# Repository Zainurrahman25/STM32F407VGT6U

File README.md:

# STM32F407VGT6U
Project STM32F4

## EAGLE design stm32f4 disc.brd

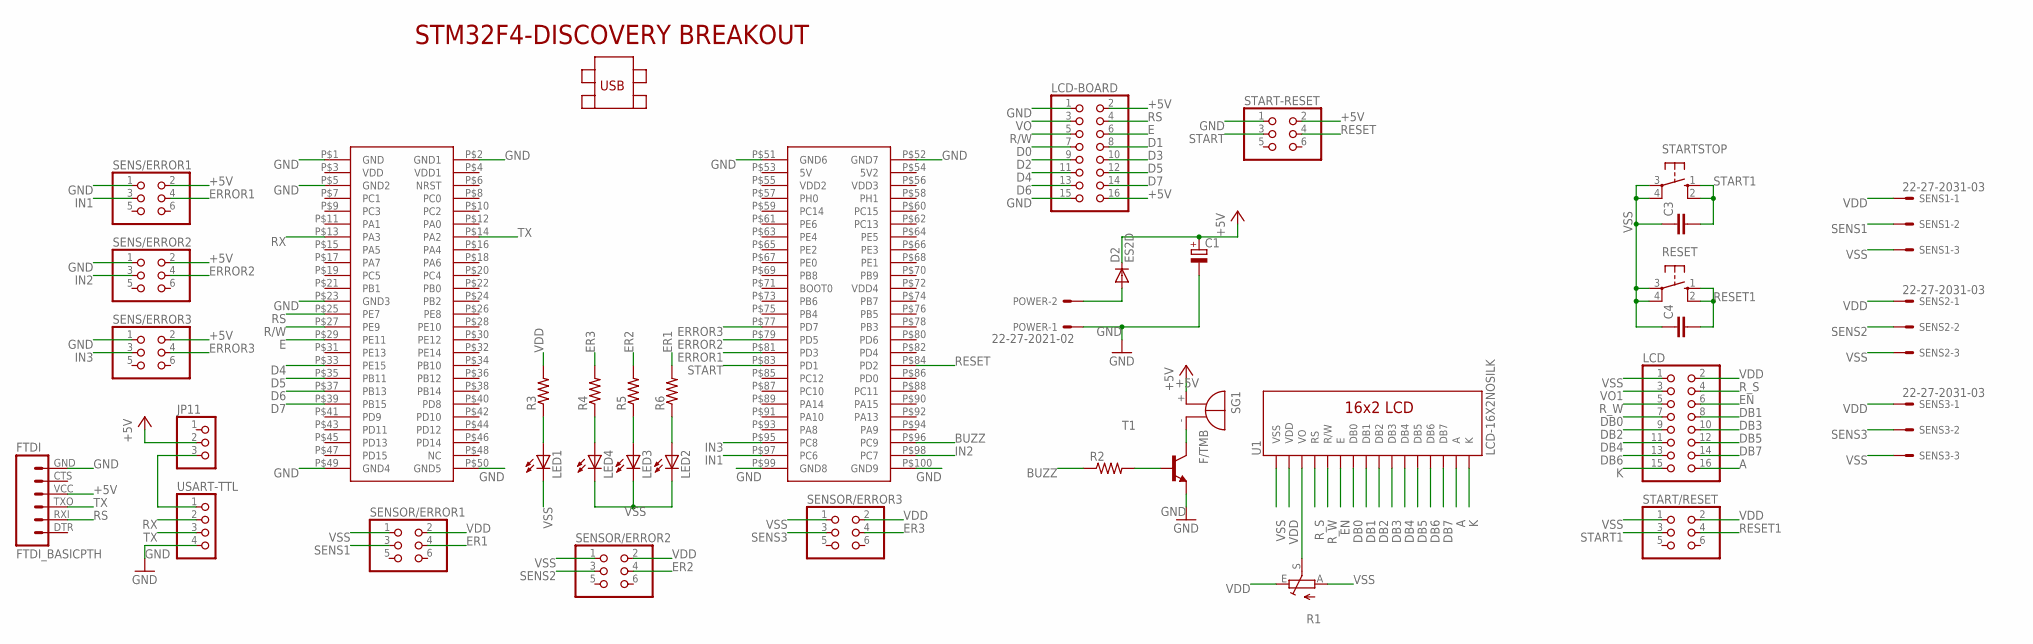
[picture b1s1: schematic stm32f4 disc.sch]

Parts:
C1: CPOL-EU140CLH-1010; 140CLH-1010
C3, C4: C-EUC0805; C0805
D2: ES2D; SMB
FTDI: FTDI_BASICPTH; FTDI_BASIC
JP11: PINHD-1X3; 1X03
LCD: PINHD-2X8; 2X08
LCD-BOARD: PINHD-2X8; 2X08
LED1, LED2, LED3, LED4: LED5MM
POWER: 22-27-2021-02; 6410-02
R1: TRIM_EU-CA6V; CA6V
R2, R3, R4, R5, R6: R-US_R0805; R0805
RESET: 40-XX; B3F-40XX
SENS1, SENS2, SENS3: 22-27-2031-03; 6410-03
SENS/ERROR1, SENS/ERROR2, SENS/ERROR3: PINHD-2X3; 2X03
SENSOR/ERROR1, SENSOR/ERROR2, SENSOR/ERROR3: PINHD-2X3; 2X03
SG1: F/TMB
START-RESET: PINHD-2X3; 2X03
START/RESET: PINHD-2X3; 2X03
STARTSTOP: 40-XX; B3F-40XX
T1: -NPN-SOT23-EBC; SOT23-EBC
U1: LCD-16X2NOSILK; LCD-16X2_NOSILK
U$1: STM32F4-DISCOVERY
USART-TTL: PINHD-1X4; 1X04

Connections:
+5V: C1.+, D2.C, FTDI.VCC (4), JP11.2, LCD-BOARD.2, LCD-BOARD.16, SENS/ERROR1.2, SENS/ERROR2.2, SENS/ERROR3.2, SG1.+, START-RESET.2
A: LCD.16, U1.15 (A)
BUZZ: R2.1, U$1.P$96 (PC9)
D0: LCD-BOARD.7
D1: LCD-BOARD.8
D2: LCD-BOARD.9
D3: LCD-BOARD.10
D4: LCD-BOARD.11, U$1.P$33 (PE15)
D5: LCD-BOARD.12, U$1.P$35 (PB11)
D6: LCD-BOARD.13, U$1.P$37 (PB13)
D7: LCD-BOARD.14, U$1.P$39 (PB15)
DB0: LCD.7, U1.7 (DB0)
DB1: LCD.8, U1.8 (DB1)
DB2: LCD.9, U1.9 (DB2)
DB3: LCD.10, U1.10 (DB3)
DB4: LCD.11, U1.11 (DB4)
DB5: LCD.12, U1.12 (DB5)
DB6: LCD.13, U1.13 (DB6)
DB7: LCD.14, U1.14 (DB7)
E: LCD-BOARD.6, U$1.P$29 (PE11)
EN: LCD.6, U1.6 (E)
ER1: R6.2, SENSOR/ERROR1.4
ER2: R5.2, SENSOR/ERROR2.4
ER3: R4.2, SENSOR/ERROR3.4
ERROR1: SENS/ERROR1.4, U$1.P$81 (PD3)
ERROR2: SENS/ERROR2.4, U$1.P$79 (PD5)
ERROR3: SENS/ERROR3.4, U$1.P$77 (PD7)
GND: C1.-, FTDI.GND (6), LCD-BOARD.1, LCD-BOARD.15, POWER.1, SENS/ERROR1.1, SENS/ERROR2.1, SENS/ERROR3.1, START-RESET.1, T1.E, U$1.P$1 (GND), U$1.P$2 (GND1), U$1.P$5 (GND2), U$1.P$23 (GND3), U$1.P$49 (GND4), U$1.P$50 (GND5), U$1.P$51 (GND6), U$1.P$52 (GND7), U$1.P$99 (GND8), U$1.P$100 (GND9), USART-TTL.4
IN1: SENS/ERROR1.3, U$1.P$97 (PC6)
IN2: SENS/ERROR2.3, U$1.P$98 (PC7)
IN3: SENS/ERROR3.3, U$1.P$95 (PC8)
K: LCD.15, U1.16 (K)
unnamed: SG1.-, T1.C
unnamed: R2.2, T1.B
unnamed: LED2.A, R6.1
unnamed: LED3.A, R5.1
unnamed: JP11.3, USART-TTL.1
unnamed: LED4.A, R4.1
unnamed: LED1.A, R3.1
unnamed: D2.A, POWER.2
unnamed: R1.S, U1.3 (VO)
R/W: LCD-BOARD.5, U$1.P$27 (PE9)
RESET: START-RESET.4, U$1.P$84 (PD2)
RESET1: C4.2, RESET.1 (S), RESET.2 (S1), START/RESET.4
RS: FTDI.RXI (2), LCD-BOARD.4, U$1.P$25 (PE7)
RX: U$1.P$13 (PA3), USART-TTL.2
R_S: LCD.4, U1.4 (RS)
R_W: LCD.5, U1.5 (R/W)
SENS1: SENS1.2, SENSOR/ERROR1.3
SENS2: SENS2.2, SENSOR/ERROR2.3
SENS3: SENS3.2, SENSOR/ERROR3.3
START: START-RESET.3, U$1.P$83 (PD1)
START1: C3.2, START/RESET.3, STARTSTOP.1 (S), STARTSTOP.2 (S1)
TX: FTDI.TXO (3), U$1.P$14 (PA2), USART-TTL.3
VDD: LCD.2, R1.E, R3.2, SENS1.1, SENS2.1, SENS3.1, SENSOR/ERROR1.2, SENSOR/ERROR2.2, SENSOR/ERROR3.2, START/RESET.2, U1.2 (VDD)
VO: LCD-BOARD.3
VO1: LCD.3
VSS: C3.1, C4.1, LCD.1, LED1.K (C), LED2.K (C), LED3.K (C), LED4.K (C), R1.A, RESET.3, RESET.4 (P1), SENS1.3, SENS2.3, SENS3.3, SENSOR/ERROR1.1, SENSOR/ERROR2.1, SENSOR/ERROR3.1, START/RESET.1, STARTSTOP.3, STARTSTOP.4 (P1), U1.1 (VSS)

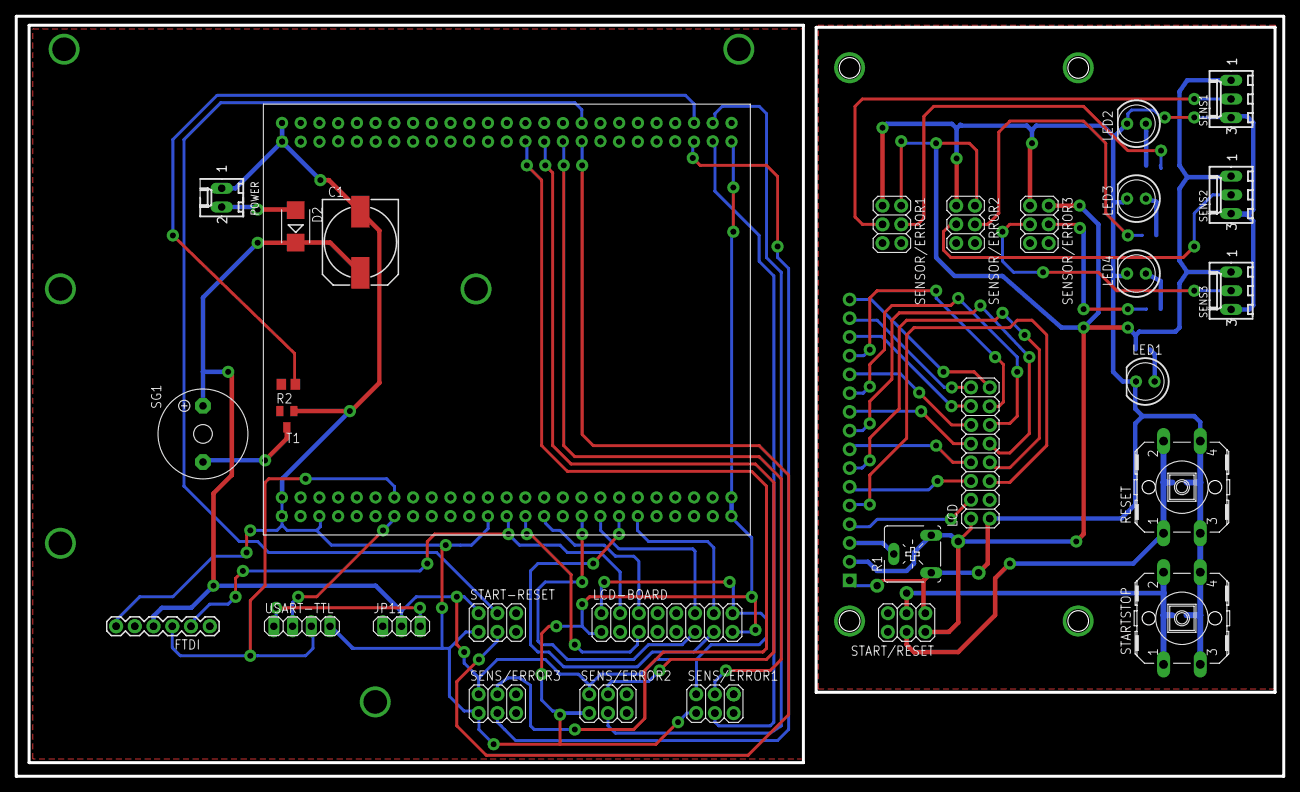
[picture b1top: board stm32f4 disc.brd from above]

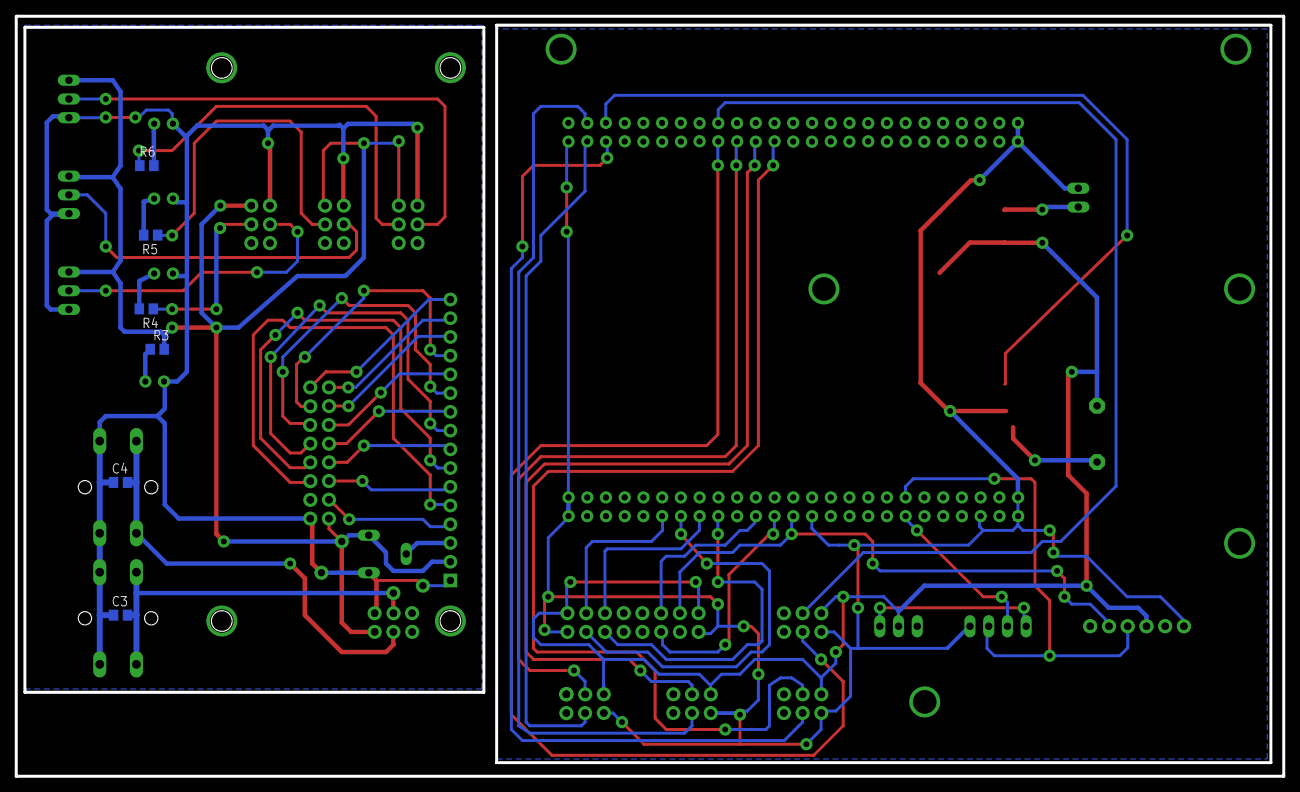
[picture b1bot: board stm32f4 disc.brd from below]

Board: 2 copper layers, 171.9 x 103.1 mm, 37 parts (6 on the bottom side), 52 nets.

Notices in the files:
parts and their libraries:
SparkFun-Displays: Licensing: Creative Commons ShareAlike 4.0 International - https://creativecommons.org/licenses/by-sa/4.0
